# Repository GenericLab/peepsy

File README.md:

# Peepsy
Simple continuity tester based on Continuity Tester by David Johnson-Davies - http://www.technoblogy.com/show?1YON

# diy-CAD Handouts
diy-CAD (do-it-yourself Children Aided Design): The core idea of the workshop-kit is tool for creative designs of printed circuit boards, introducing basic concepts of Open Hardware being something to re-design for your own use. 

Read more about the creative PCB design methodology on this wiki: https://www.hackteria.org/wiki/Diy-CAD

## the schematics

## the BOM also know as the parts

# GAPS Workshops
## GAPS (GaPiSen) | gambar pisibi-mu sendiri - Creative PCB-design Workshop with Diy-CAD, Lifepatch 30. June 2022

## GAPS - Creative PCB-design Workshop, Electronic Wonderland August 2022

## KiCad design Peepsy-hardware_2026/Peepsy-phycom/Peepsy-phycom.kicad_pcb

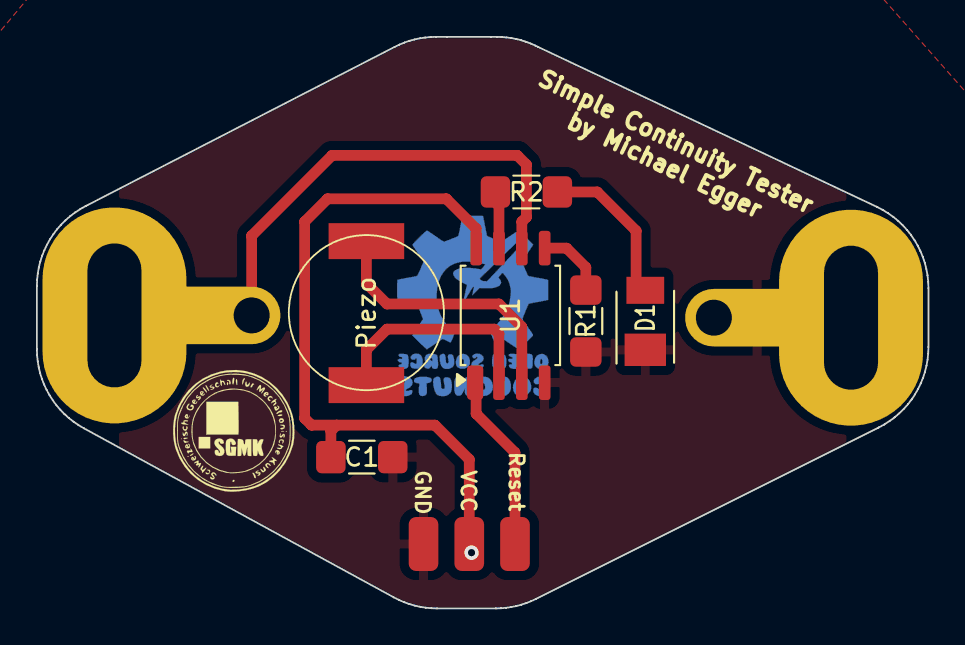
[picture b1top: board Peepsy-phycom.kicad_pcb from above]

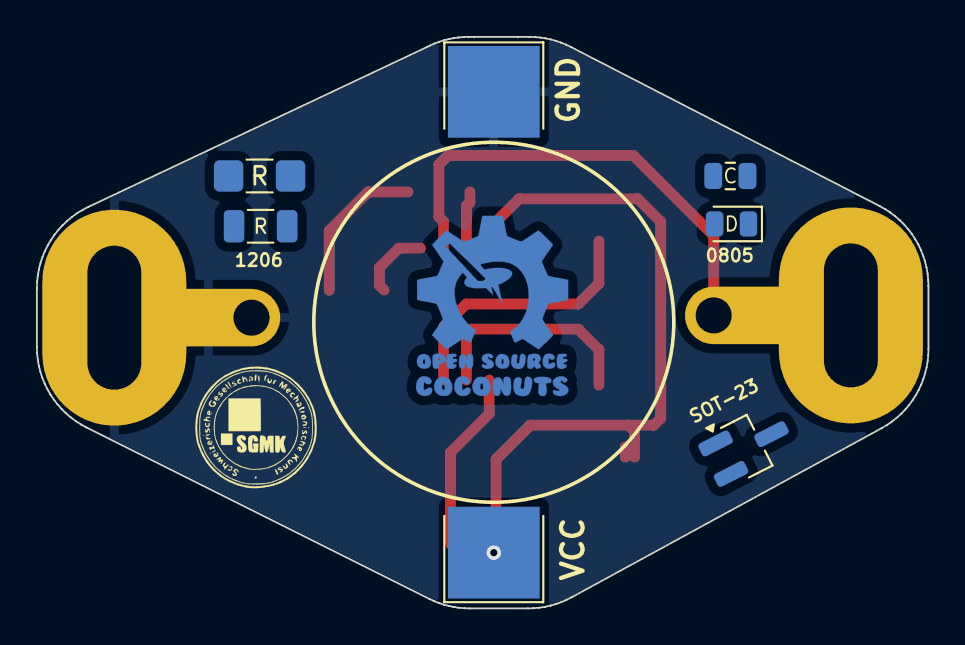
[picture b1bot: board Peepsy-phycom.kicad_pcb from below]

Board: 2 copper layers, 49.5 x 31.8 mm, 14 parts (5 on the bottom side), 9 nets.

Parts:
BT1: Battery_Cell; BatteryHolder_Keystone_1x2032
C: C_0805_2012Metric
C1: C; C_1210_noGND
D: LED_0805_2012Metric
D1: Signal; LED_PLCC_2835_Handsoldering
J1, J2: Probe; PeepsyPad_noGND
J3: Conn_01x03_Pin; smd-3pin
Piezo: Speaker_Crystal; Buzzer_CUI_CPT-9019S-SMT
R, R1, R2: R; R_1206_noGND
Ref**: Val**; Coconut_logo_sm
U1: ATtiny85-20SU; SOIC-8_Attiny85

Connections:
/Probe: J1.1, U1.6 (PB1)
GND: BT1.2 (-), C1.2, D1.1 (K), J2.1, J3.1, R1.1, U1.4 (GND)
unnamed: D1.2 (A), R2.1
unnamed: J3.3, U1.1 (~RESET/PB5)
unnamed: R1.2, U1.5 (AREF/PB0)
unnamed: R2.2, U1.7 (PB2)
unnamed: Piezo.1, U1.2 (XTAL1/PB3)
unnamed: Piezo.2, U1.3 (XTAL2/PB4)
VCC: BT1.1 (+), C1.1, J3.2, U1.8 (VCC)

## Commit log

2022-06-30 adding diy-CAD files
2022-08-12 more stuffs
2022-08-16 adding photos
2022-09-27 adding panda pisibi and new laminates v0.4
2022-09-27 new laminates v0.4
2022-10-14 fix link to source
2024-09-11 Soldering instructions for PandaClaw Peepsy
2026-06-30 adding new laminates form phycom and coconuts
2026-06-30 renaming and adding new hardware
